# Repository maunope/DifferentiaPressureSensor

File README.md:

# ESP32-S3 Differential Pressure Datalogger

This project is a datalogger built on the ESP32-S3 platform using the ESP-IDF framework. It's designed to read environmental data from a BMP280 sensor, display it on an OLED screen with a menu-driven interface, and log the data to an SD card. The system uses a DS3231 Real-Time Clock (RTC) for accurate timestamping and exposes the SD card as a USB Mass Storage Device for easy data access.

Please refer to the following main guides for usage guidance and documentation:

*   **[User Interface Guide](UI_GUIDE.md)**: A complete guide to the on-screen menu system and controls.
*   **[Web UI Guide](WEB_UI.md)**: Instructions for using the web interface to manage files.
*   **[Software Architecture](SOFTWARE_ARCHITECTURE.md)**: An in-depth look at the software design, tasks, and communication mechanisms.
*   **[Board Design](BOARD_DESIGN.md)**: Details on the custom PCB, hardware components, and pinout.

## Overview

### Key Features

*   **Sensor Datalogging**: Periodically reads:
    *   Temperature and atmospheric pressure from a BMP280 sensor.
    *   Differential pressure from an Omron D6F-PH sensor.
    *   LiPo battery voltage and percentage.
    *   Device uptime in seconds.
*   **Dual-Mode Data Smoothing**: Configurable Kalman filtering is applied to all sensor readings. The system uses two distinct sets of filter parameters for "Normal" and "High-Frequency" logging modes. All parameters (`kf_*_q`, `kf_*_r`, `kf_*_q_hf`, `kf_*_r_hf`) can be customized in `config.ini`. If high-frequency (`_hf`) parameters are omitted, the system automatically calculates sensible defaults based on the normal-frequency values.
*   **SD Card Storage**: Logs sensor data to CSV files on an SD card, with support for file rotation based on size (1MB limit, approx. 2 weeks of recording at 1 point per minute).
*   **Real-Time Clock (RTC)**: Utilizes a DS3231 RTC for accurate timestamps. The system can synchronize its time from the RTC on startup.
*   **OLED Display & UI**: Features a menu-driven user interface on an OLED display, controlled by a rotary encoder with a push-button. The UI displays:
    *   Real-time sensor data (temperature, pressure, differential pressure, battery status).
    *   Current local timestamp (CET/CEST).
    *   SD card write status.
    *   Persistent status icons for battery level, charging status, and SD card write errors.
    *   A settings menu to manage the RTC, SD card, view configuration, and display a QR code linking to the project repository.
*   **NTP Time Sync**: Can synchronize the RTC with an NTP server over Wi-Fi.
*   **Web Server**: Can start a web server to allow downloading and previewing logged data files directly from a web browser.
*   **Multiple Sampling Modes**: Supports "Normal", "High Frequency", and "Paused" logging modes, selectable via the UI.
*   **Robust Power Management**: Implements a command-driven deep sleep cycle to conserve battery. The datalogger task explicitly signals when it's safe to sleep, preventing race conditions and ensuring data integrity. The device wakes up on a timer for the next log or via user interaction. A safety threshold on battery voltage avoids data corruption when measured battery voltage is too low to guarantee stable power to the 3.3V rail.
*   **Web File Management**: The web interface allows users to list, preview, download, and delete log files directly from the device.
*   **Exclusive File System Access**: To prevent data corruption, the system ensures that only one component (Datalogger, Web Server, or USB Mass Storage) can access the SD card at a time. For example, starting the web server will pause the datalogger, and connecting the device to a PC will disable both the web server and the datalogger.
*   **Configuration & Persistence**:
    *   **Permanent Settings**: Key parameters like sleep intervals, Wi-Fi credentials, and sensor models can be configured via a `config.ini` file on the SD card. These settings are loaded into flash memory and persist across reboots.
    *   **Session Settings**: UI-selected modes (like "High Frequency" or "Paused") are stored in RTC memory and persist through deep sleep cycles, but will be reset to their default values after a full power cycle or reboot.
*   **RTOS-based**: Built on FreeRTOS, with separate tasks for data logging and UI rendering for a responsive and robust application.

### Hardware Components

*   **Microcontroller**: ESP32-S3
*   **Sensors**:
    *   BMP280: Barometric Pressure and Temperature (I2C)
    *   Omron D6F-PH: Differential Pressure (I2C)
*   **Storage**:
    *   MicroSD Card Slot (SPI)
*   **Display**:
    *   OLED Display (I2C)
*   **User Input**:
    *   Rotary Encoder with Push-button
*   **Timekeeping**:
    *   DS3231 Real-Time Clock (I2C)
*   **Power**:
    *   LiPo Battery with a voltage divider for monitoring.

For more details on the custom PCB, see the [board design documentation](BOARD_DESIGN.md).

## Hardware Notes

### DS3231 RTC Configuration

Please be aware that this firmware automatically configures any connected DS3231 Real-Time Clock with specific default settings upon boot. These settings are optimized for low-power operation and resilience. For details on the exact register values being set, please refer to the `readme.md` file located in the `lib/i2c_ds3231/` directory.

### Usage

1.  **Configuration**: Copy the `config_sample.ini` file to the root of your SD card and rename it to `config.ini`. Edit this file to set your Wi-Fi credentials, sensor model, and other parameters.
2.  **Operation**: The device is controlled with the rotary encoder and its built-in push-button. For a detailed explanation of the menu system and on-screen information, please see the User Interface Guide.
3.  **Web Interface**: When the web server is active, you can manage files from your browser. See the Web UI Guide for more details.
## Software & Libraries

*   **Framework**: ESP-IDF
*   **RTOS**: FreeRTOS
*   **Component Management**: Dependencies like `qrcode` and `tinyusb` are managed by the ESP-IDF Component Manager via the `idf_component.yml` file. The `esp_tinyusb` component for USB Mass Storage is enabled and configured directly through `menuconfig`, with settings reflected in the PlatformIO build profiles.
*   **Software Architecture**: The project is built on a multi-tasking architecture using FreeRTOS. For a detailed explanation of the tasks and how they communicate, see the Software Architecture Guide.
*   **Custom Libraries (located in `lib/`)**: This project uses a modular structure with several custom libraries. Click on a library name to see its specific documentation.
    *   `config_manager`: Handles loading configuration from an INI file.
    *   `i2c_bmp280`: Driver for the BMP280 sensor.
    *   `i2c_d6fph`: Driver for the Omron D6F-PH sensor.
    *   `i2c_ds3231`: Driver for the DS3231 RTC.
    *   `i2c_oled`: Driver for the OLED display.
    *   `kalman`: kalman filter implementation.
    *   `lipo_battery`: Logic for reading battery voltage.
    *   `ntp_client`: Helper for synchronizing time from an NTP server.
    *   `rotary_encoder`: Driver for the rotary encoder input.
    *   `spi_sdcard`: High-level manager for SD card operations and USB MSC.
    *   `ui`: Manages the complete user interface, menu, and pages. See the UI Guide.
    *   `web_server`: Provides a web interface for downloading log files. See the Web UI Guide.
    *   `wifi_manager`: Centralizes Wi-Fi connection and disconnection logic.

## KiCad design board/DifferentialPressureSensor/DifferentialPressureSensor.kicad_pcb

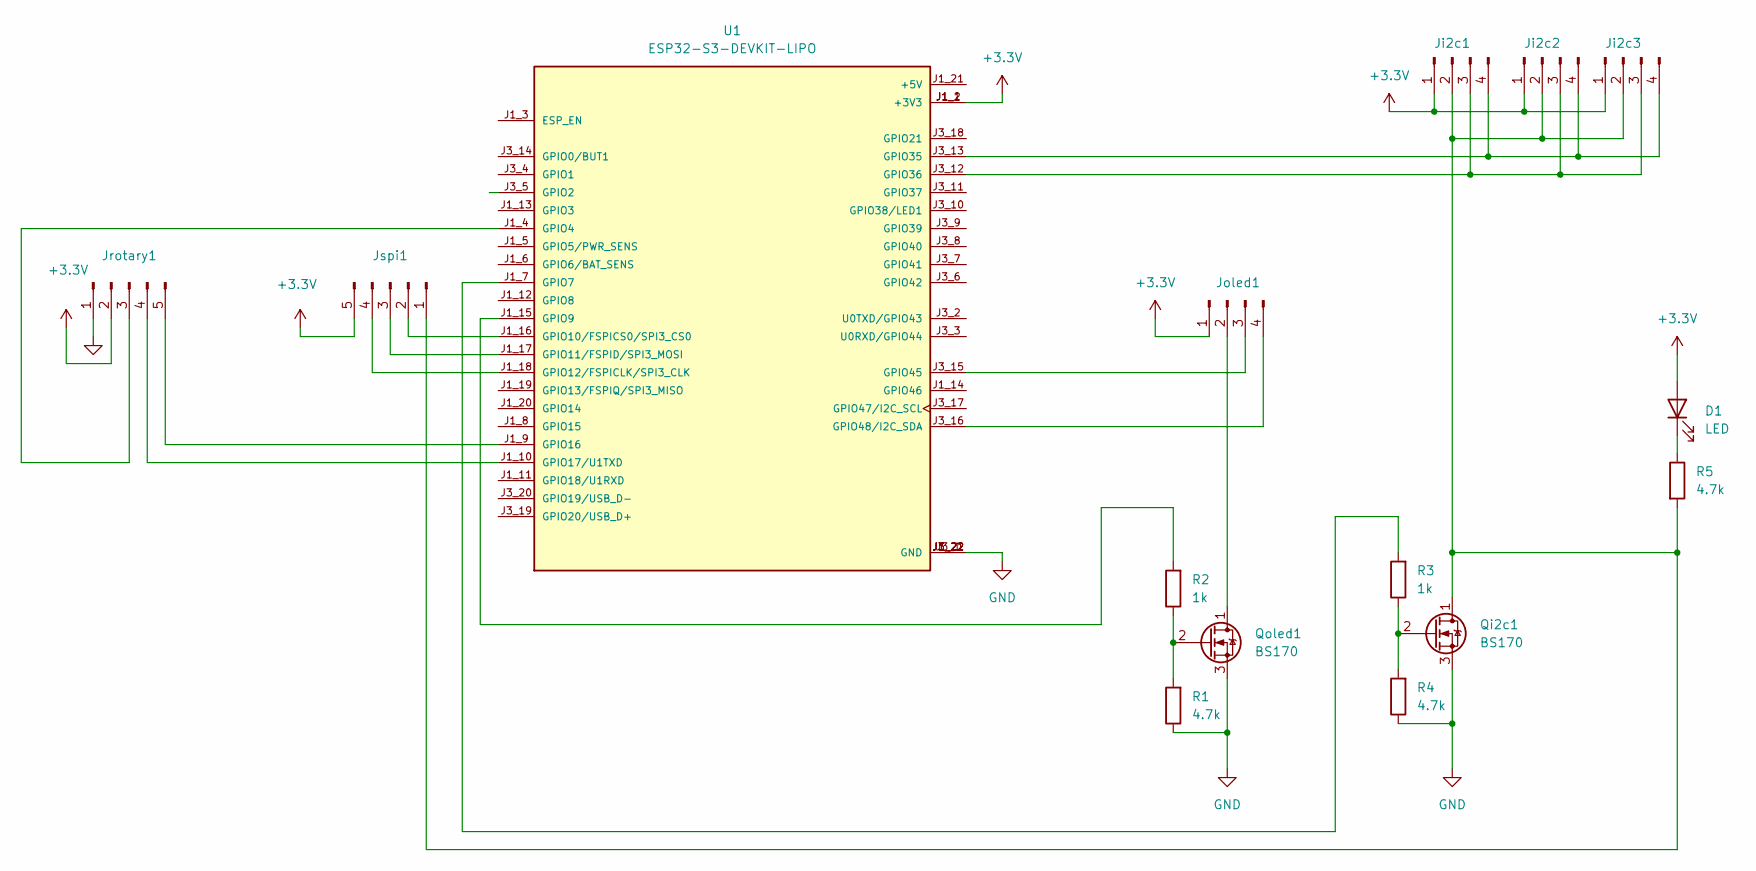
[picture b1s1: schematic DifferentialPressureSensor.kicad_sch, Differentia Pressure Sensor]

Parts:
D1: LED; LED_D3.0mm
Ji2c1, Ji2c2, Ji2c3: Conn_01x04_Pin; PinHeader_1x04_P2.00mm_Vertical
Joled1: Conn_01x04_Pin; PinHeader_1x04_P2.00mm_Vertical
Jrotary1: PinHeader_1x05_P2.00mm_Vertical
Jspi1: PinHeader_1x05_P2.00mm_Vertical
Qi2c1: BS170; TO-92_Inline
Qoled1: BS170; TO-92_Inline
R1, R4, R5: 4.7k; R_Axial_DIN0207_L6.3mm_D2.5mm_P7.62mm_Horizontal
R2, R3: 1k; R_Axial_DIN0207_L6.3mm_D2.5mm_P7.62mm_Horizontal
U1: ESP32-S3-DEVKIT-LIPO; XCVR_ESP32-S3-DEVKIT-LIPO; PARTREV B

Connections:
+3.3V: D1.2 (A), Ji2c1.1, Ji2c2.1, Ji2c3.1, Joled1.1, Jrotary1.2, Jspi1.5, U1.J1_1 (+3V3), U1.J1_2 (+3V3)
GND: Jrotary1.1, Qi2c1.3 (S), Qoled1.3 (S), R1.1, R4.1, U1.J1_22 (GND), U1.J3_1 (GND), U1.J3_21 (GND), U1.J3_22 (GND)
unnamed: D1.1 (K), R5.1
unnamed: Ji2c1.2, Ji2c2.2, Ji2c3.2, Jspi1.1, Qi2c1.1 (D), R5.2
unnamed: Ji2c1.3, Ji2c2.3, Ji2c3.3, U1.J3_12 (GPIO36)
unnamed: Ji2c1.4, Ji2c2.4, Ji2c3.4, U1.J3_13 (GPIO35)
unnamed: Joled1.2, Qoled1.1 (D)
unnamed: Joled1.3, U1.J3_15 (GPIO45)
unnamed: Joled1.4, U1.J3_16 (GPIO48/I2C_SDA)
unnamed: Jrotary1.3, U1.J1_4 (GPIO4)
unnamed: Jrotary1.4, U1.J1_10 (GPIO17/U1TXD)
unnamed: Jrotary1.5, U1.J1_9 (GPIO16)
unnamed: Jspi1.2, U1.J1_16 (GPIO10/FSPICS0/SPI3_CS0)
unnamed: Jspi1.3, U1.J1_17 (GPIO11/FSPID/SPI3_MOSI)
unnamed: Jspi1.4, U1.J1_18 (GPIO12/FSPICLK/SPI3_CLK)
unnamed: Qi2c1.2 (G), R3.1, R4.2
unnamed: Qoled1.2 (G), R1.2, R2.1
unnamed: R3.2, U1.J1_7 (GPIO7)
unnamed: R2.2, U1.J1_15 (GPIO9)

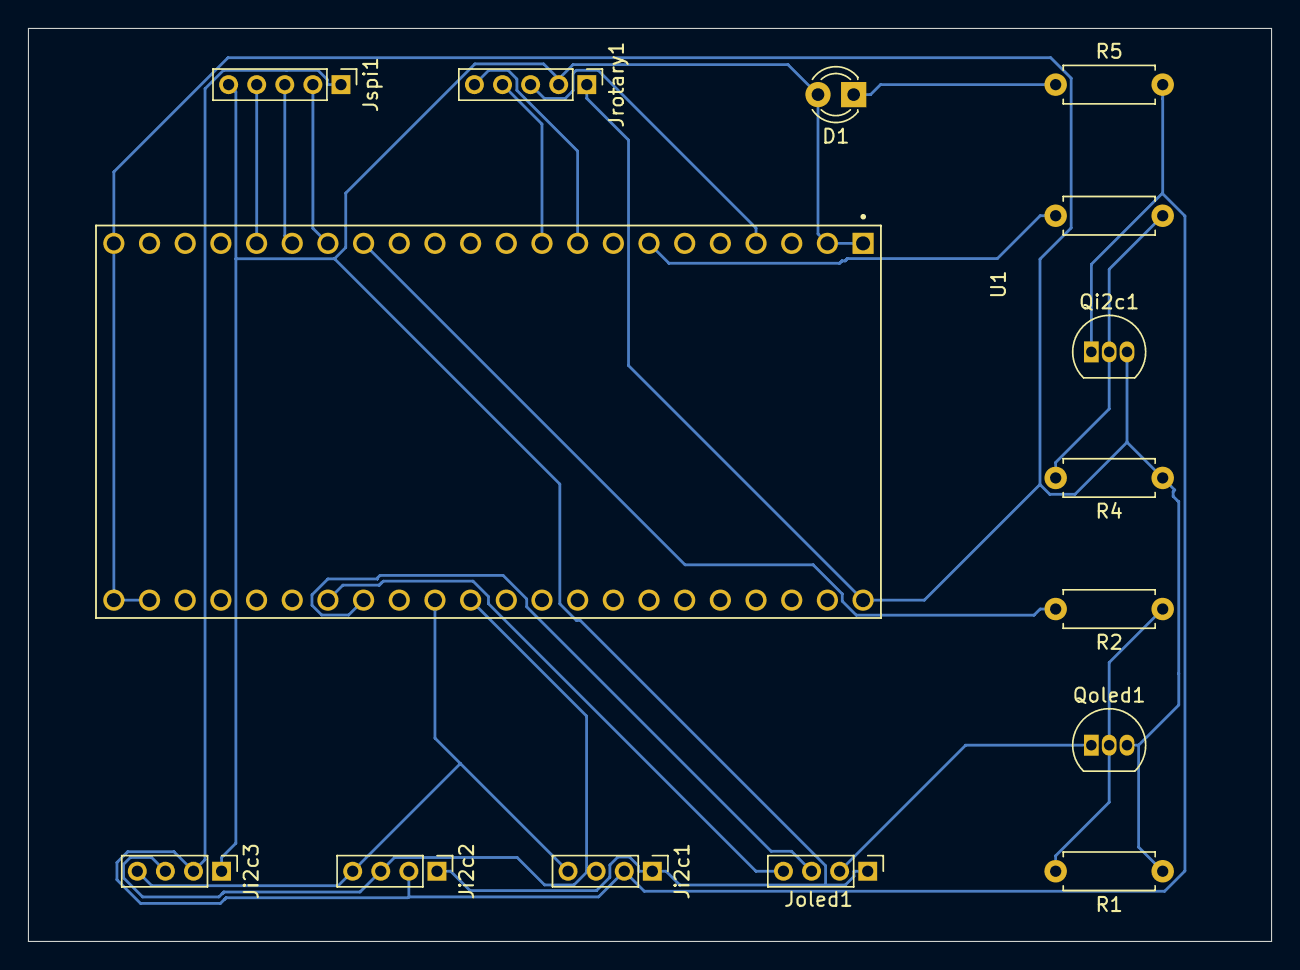
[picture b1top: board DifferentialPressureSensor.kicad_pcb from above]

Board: 2 copper layers, 88.5 x 65.0 mm, 15 parts (0 on the bottom side), 19 nets.

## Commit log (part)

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2025-08-11 first upload (expect turmoil/crap in the next few commits :-D)
2025-08-11 gitignore
2025-08-11 fixed gitignore
2025-08-11 first hello world, reads pressure/temperature from a BMP180 i2c breakout board and prints it to serial
2025-08-11 saving last without lib on i2c lcd
2025-08-11 i2c LCD
2025-08-12 refactor files to libs
2025-08-12 removed useless lines
2025-08-27 feat: Add I2C OLED display support and SPI SD card functionality
    - Implemented I2C communication for OLED display with functions to initialize, clear, and write text.
    - Added SPI SD card support with initialization and CSV writing capabilities.
    - Refactored rotary encoder task for improved state management and responsiveness.
    - Updated main application to integrate OLED display and SD card logging for temperature and pressure readings from BMP180 sensor.
    - Enhanced error handling and logging for SD card operations.
    - Cleaned up I2C configuration for better organization and clarity.
2025-08-29 added tinyusb lib, still not used, just added idf_component.yml and checked that compile/link works
2025-09-04 sd card mount working
2025-09-15 fairly crude and non-thread safe handling of MSC/local write priority, but works. note: writes are blocked as long as the micro is hooked up to a pc, even if it is ejected. not sure about what happen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
2025-09-18 temp - broken state
2025-09-18 crude, but functioning, fuckups protection on sdcard. apparently tud_ready() is the only method that reliably works, callbacks don't work reliably, tud_mounted will stay true indefinitely once it wen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
2025-09-19 temp, works
2025-09-19 switched to espressif/esp_tinyusb 2.0.0, which sucks ass every bit as bad as 1.7.6 when it comes to MSC mount/unmount callbacks but, apparently, does a better job at figuring if the cable is still co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
2025-09-20 added release build conf
2025-09-20 improved usb write speed 10X, to approx 5megabit, swapped SPI pins, created release build conf, reenabled jtag on debug one
2025-09-23 -added rtc module support -Refactor sensor buffer structure and integrate DS3231 RTC for timestamp management; -update SD card write functionality to include timestamps from rtc, and use global share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
    all this is amazingly beautiful BUT, sends the esp32 in reboot loop.
2025-10-02 Refactor SD card logging and UI rendering
    - Updated `spi_sdcard_write_csv` to remove filename parameter and implement file rotation based on size.
    - Enhanced error handling and logging for SD card operations.
    - Introduced a new `datalogger_task` to handle periodic sensor readings and logging to SD card.
    - Improved UI rendering functions to support flicker-free updates and command feedback.
    - Added functionality to set RTC time to build time during initialization.
    - Updated configuration for FAT filesystem to support long filenames.
2025-10-02 restored bmp280
2025-10-08 Enhance battery management features: - Added support for external power detection. - Updated battery reader initialization to include power GPIO. - Improved logging to include battery voltage, percen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
2025-10-08 Add SD card file count and free space retrieval functions; update UI and command handling; added SD format feature
2025-10-09 added olimex esp32 s3 lipo as a module
2025-10-09 first jab at sleep mode
2025-10-09 first jab at kicad design
2025-10-10 feat: Add sensor data refresh command and enhance rotary encoder functionality
    - Introduced APP_CMD_REFRESH_SENSOR_DATA command in buffers.h for refreshing sensor data.
    - Made gpio_isr_handler public in rotaryencoder.c and added rotaryencoder_enable_wakeup_source function to configure GPIO wake-up sources.
    - Updated rotaryencoder.h to declare new functions and ensure proper IRAM attributes.
    - Enhanced UI rendering logic in ui_render.c to handle sleep and wake events, including new UI_EVENT_PREPARE_SLEEP and UI_EVENT_WAKE_UP events.
    - Refactored datalogger_task.c to improve sensor data updating logic and added a command queue for forced refresh commands.
    - Updated main.c to handle new command
2025-10-10 removed useless file
2025-10-10 removed bmp18'0 support
2025-10-10 fixed timezone display and set everything internal to gmt
2025-10-10 feat: Add time conversion utilities for CET/CEST and update timestamp handling
2025-10-12 power off off devices when sleeping pause and resume functionality for datalogger writes
2025-10-12 feat: Add last successful write timestamp to sensor buffer and update related logic
2025-10-12 refactor: Rename initialization functions for clarity and consistency
2025-10-12 first low power mode holding together , with timeouts and wakeups working
2025-10-13 feat: Add BMP280 sensor re-initialization function to improve reliability
2025-10-13 feat: Enhance I2C initialization for BMP280 and DS3231 with default address macros and improve rotary encoder handling refactored rotary encoder to avoid harcoded dependencies resolved warnings on ui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
2025-10-13 feat: Add detailed documentation for BMP280, DS3231, OLED, and rotary encoder functions
2025-10-13 feat: Pass BMP280 device handle to datalogger task and update sensor buffer function signature
2025-10-13 fix: Remove IRAM_ATTR attribute from gpio_isr_handler function declaration to correct complilation warning
2025-10-14 first jab at differential sensor
2025-10-17 -Enhance Datalogger Functionality and Update Rotary Encoder Configuration - Updated the datalogger_task to initialize sensor readings after resuming from sleep, ensuring fresh data is captured. - Cha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
2025-10-17 deep sleep
2025-10-18 feat: Implement configuration management and UI updates for differential pressure sensor
2025-10-18 fix: Enhance OLED power management and deep sleep logic for UI task handling
2025-10-18 feat: Add global sensor buffer and initialization event group for improved data handling
2025-10-19 feat: Add NTP client for RTC synchronization and update configuration handling
2025-10-19 fixed differential pressure sensor (now it works!), made the omron sensor model parametric, moved i2c oled o he beginning of main,
2025-10-19 fix: Validate Wi-Fi SSID configuration before NTP synchronization
2025-10-19 doc overhaul
2025-10-19 feat: Add PCB design documentation for Differential Pressure Datalogger
2025-10-20 feat: Add web server functionality and UI integration
    - Updated UI guide to include web server navigation and functionality.
    - Introduced web server status management in buffers.h.
    - Refactored NTP client to utilize the new Wi-Fi manager for connection handling.
    - Created web server implementation with file listing and download capabilities.
    - Added web server commands to the application command set.
    - Enhanced main application logic to manage web server state and interactions with the datalogger.
2025-10-20 code refactor
2025-10-20 feat: Improve rotary encoder debounce handling and logging functionality
2025-10-20 feat: Enhance UI with persistent status icons and improve OLED drawing functions
    battery indicard, write failure indicator
2025-10-20 fix ui
2025-10-20 improvements to web ui
2025-10-20 Refactor SD card access management and enhance web server functionality
    - Updated README.md to clarify exclusive file system access rules.
    - Enhanced SOFTWARE_ARCHITECTURE.md with detailed SD card access arbitration.
    - improved exclusive file system access in the main task to prevent data corruption.
    - Improved web server to serve a modern index.html page with file management features.
    - Added API endpoints for file listing and deletion, ensuring safe operations.
    - Implemented Wi-Fi manager deinitialization to free resources on shutdown.
2025-10-21 Add High-Frequency Mode support with UI and configuration updates
2025-10-21 Enhance SD card logging functionality with file rotation and CSV header support
2025-10-21 restored optimization in build flags and updated doc
2025-10-22 Refactor datalogger task and buffer management
    - Removed unused datalogger status from sensor buffer.
    - Introduced uptime tracking in the sensor buffer.
    - Updated datalogger task to include uptime in CSV logs.
    - Simplified command handling for pausing and resuming datalogger.
    - Improved sleep logic to ensure proper state management before entering deep sleep.
    - Added smart sleep duration calculation based on logging intervals.
2025-10-22 page title
2025-10-22 crash on slep fix
2025-10-22 Enhance web server functionality and UI updates
    - Improved web server page to allow downloading and previewing logged data files.
    - Added preview feature for CSV files with a user-friendly interface.
    - Updated README and UI guide to reflect new features.
    - Refactored code for better readability and maintainability.
    - fixed sleep logic flaws
    - INFINTE SCROLL ON PREVIEW STILL BROKEN
2025-10-24 feat(datalogger): add file deletion command and update CSV header
    - Added a new command (DATALOGGER_CMD_DELETE_FILE) to the datalogger task for deleting specified log files.
    - Updated the CSV header to use "datetime_local" instead of "datetime_cet".
    - Modified the logging format to exclude the timezone in the local time string.
    - Removed unnecessary web server pause logic during startup and ensured proper handling of USB connection events.
    - Implemented file existence check and deletion before renaming the configuration file to prevent conflicts.
    - ensure broken conf files are just discarded without afecting curent conf
2025-10-24 set max file size to 5mb
2025-10-24 edits
2025-10-24 "scroll to" finally works fine
2025-10-24 solved flicker on loading screen
2025-10-24 display of current data on web ui
2025-10-24 finalized missing sensors management
2025-10-24 updated lipo battery gauge
2025-10-24 optimization to file list refresh
2025-10-24 refactor file loading mechanism to use a signature for change detection and reduce refresh interval to 10 seconds
2025-10-25 ui improvements
2025-10-25 fix naming
2025-10-25 sparklines
2025-10-25 switched to kPA for absolute pressure, improvements to sparkllines
2025-10-25 massive file names tidy up and doc
2025-10-25 scale bar in web ui
2025-10-25 ui and doc
2025-10-25 Update README and web UI documentation; adjust SD card file size limit to 1MB and clarify scrolling behavior in the web interface.
2025-10-25 ui fix
2025-10-25 ui optimizations and corrected a bug on file format
2025-10-25 ui fixes
2025-10-26 Fix GPIO pin assignments for SD card and improve pressure reading handling in datalogger
2025-10-26 doc and final fixes to UI
2025-10-27 favicon
2025-10-27 battery treshold implementation
2025-10-27 updates to config sample doc
2025-10-28 added a feaure to reset ds3231 configuration on each boot.
2025-10-28 date conversion bug, missed web server disable bug
2025-10-28 ui MSC mode icon (replaces frequency icons when plugged), refactor to sensor page, removal on non reentrant function usage, refactor of data refresh logic, corrected flaw on batteyr status update, cp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
2025-10-28 new icon
2025-10-28 corrected string
2025-10-28 first jab at bitmap drawing and reviseda alphabet
2025-10-29 drawbitmap adoption
2025-10-29 Enhance web server functionality and bitmap management
    - Added mutex for scratch buffer in web server to prevent race conditions during file operations.
    - Improved README with detailed explanations of web server features and memory management.
    - Updated bitmap handling in `bitmaps.h` and added new bitmap Excel file.
    - Refactored sleep mode rendering to optimize power usage.
    - Fixed error handling in web server startup process.
    - Added "bitmap editor" xlsx file
2025-10-29 added icons to web ui
2025-10-29 ui updates
2025-10-29 tidied up kpa/pa conversion, corrected couple of UI flaws
2025-10-31 fixed pin numbers, applied optimizations to build file, improved debouncing of rotary encoder
2025-11-01 updated pins on sch file and completed routing of PCB, sucks bad, but holds togeter with 1 layer only :-D
2025-11-02 fixed error on schematic, applied auto routing, created components bom
2025-12-16 first jab at kalman filtering
2025-12-16 moved kalman status to rtc mem and added seeding
2025-12-17 fix to precision in kalman filter to address wonky pressure reads
2025-12-17 different configurations for HF and LF polling
2025-12-17 fix to hf polling parameters
2025-12-17 documentationfix
2025-12-17 fixed a corner case: deletion of the currently active file
2025-12-19 tunin g to kalman, type cast fix on pressure sensor read, last write timestamp persisted across sleeps
